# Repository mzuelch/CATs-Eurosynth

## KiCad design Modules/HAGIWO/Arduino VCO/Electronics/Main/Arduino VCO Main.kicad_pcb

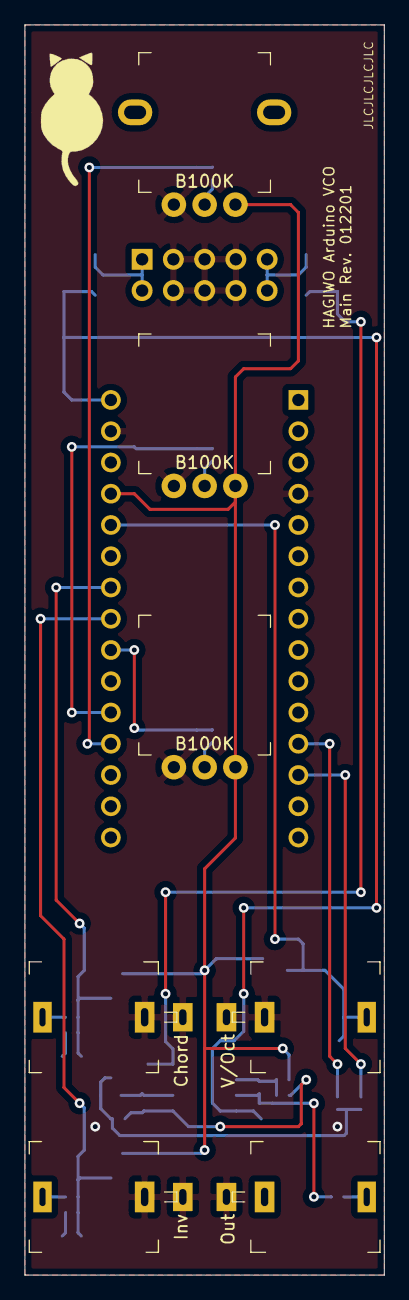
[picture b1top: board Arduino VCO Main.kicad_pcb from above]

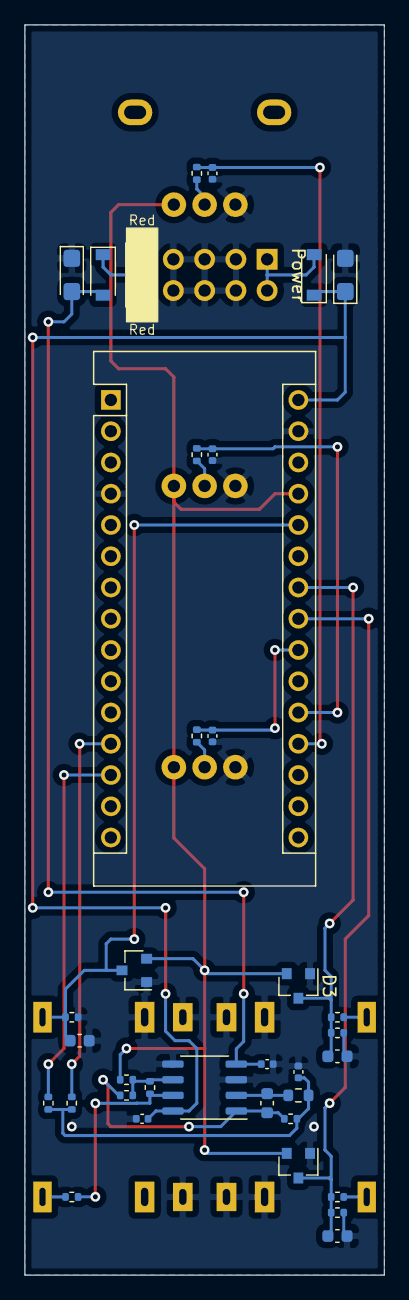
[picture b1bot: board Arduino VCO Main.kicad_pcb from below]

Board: 2 copper layers, 29.2 x 101.6 mm, 43 parts (36 on the bottom side), 25 nets.

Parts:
A1: Arduino_Nano_v3.x; Arduino_Nano
C1, C11: 10µ; CP_EIA-3216-18_Kemet-A
C2, C3, C4: 10n; C_0402_1005Metric
C5, C7, C9: 68n; C_0603_1608Metric
C6: 3.3n; C_0603_1608Metric
C8: 22n; C_0402_1005Metric
C10, C12: 100n; C_0402_1005Metric
D1, D6: B5819W SL; D_SOD-123
D2, D3, D4: BAV99; SOT-23
J1: Power; Power_2x5_Vertical
J2: V/Oct; Jack_3.5mm_QingPu_WQP-PJ301M-12
J3: Inv; Jack_3.5mm_QingPu_WQP-PJ301M-12
J4: Out; Jack_3.5mm_QingPu_WQP-PJ301M-12
J5: Chord; Jack_3.5mm_QingPu_WQP-PJ301M-12
P1: B100K; Potentiometer_AlpsAlpine_RK09L1140
P2, P3: B100K; Potentiometer_AlpsAlpine_RK09L1140_oS
R1, R2, R3, R9, R12, R15: 1k; R_0402_1005Metric
R4, R8, R10, R11, R14, R16: 100k; R_0402_1005Metric
R5: 499k; R_0402_1005Metric
R6: 3k9; R_0402_1005Metric
R7: 7k5; R_0402_1005Metric
R13: 2k7; R_0603_1608Metric
U1: TL072CDT; SO-8_3.9x4.9mm_P1.27mm

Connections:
+5V: A1.27, D2.2, D3.2, D4.2, P1.CW, P2.CW, P3.CW, R16.2
+12V: A1.30, C1.1, C10.1, D1.1, U1.8
-12V: C11.2, C12.2, D6.2, U1.4
A0: A1.19, C2.1, R1.1
A1: A1.20, C3.1, R2.1
A3: A1.22, C4.1, R3.1
A4: A1.23, C7.1, D2.3, R8.1, R9.2
A5: A1.24, C9.1, D3.3, R11.1, R12.2
A7: A1.26, C5.1, D4.3, J2.T, R4.1
D9: A1.12, R6.2
D10: A1.13, R5.2
GND: A1.4, A1.29, C1.2, C2.2, C3.2, C4.2, C5.2, C7.2, C8.2, C9.2, C10.2, C11.1, C12.1, D2.1, D3.1, D4.1, J1.GND, J2.S, J2.TN, J3.S, J3.TN, J4.S, J5.S, J5.TN, P1.CCW, P2.CCW, P3.CCW, R4.2, R8.2, R11.2, U1.3, U1.5
unnamed: C6.1, R7.2, R14.2, U1.1
unnamed: C6.2, R13.1, U1.2
unnamed: C8.1, R5.1, R6.1, R7.1, R13.2
unnamed: D1.2, J1.+12V
unnamed: D6.1, J1.-12V
unnamed: J3.T, R9.1
unnamed: J4.T, R15.1
unnamed: J5.T, R12.1
unnamed: P1.W, R1.2
unnamed: P2.W, R2.2
unnamed: P3.W, R3.2
unnamed: R10.1, R15.2, U1.7
unnamed: R10.2, R14.1, R16.1, U1.6

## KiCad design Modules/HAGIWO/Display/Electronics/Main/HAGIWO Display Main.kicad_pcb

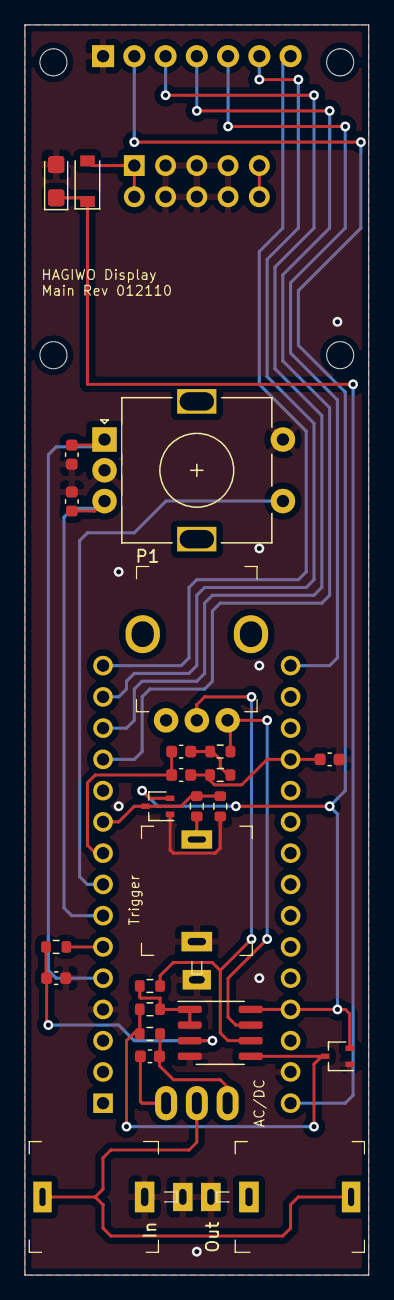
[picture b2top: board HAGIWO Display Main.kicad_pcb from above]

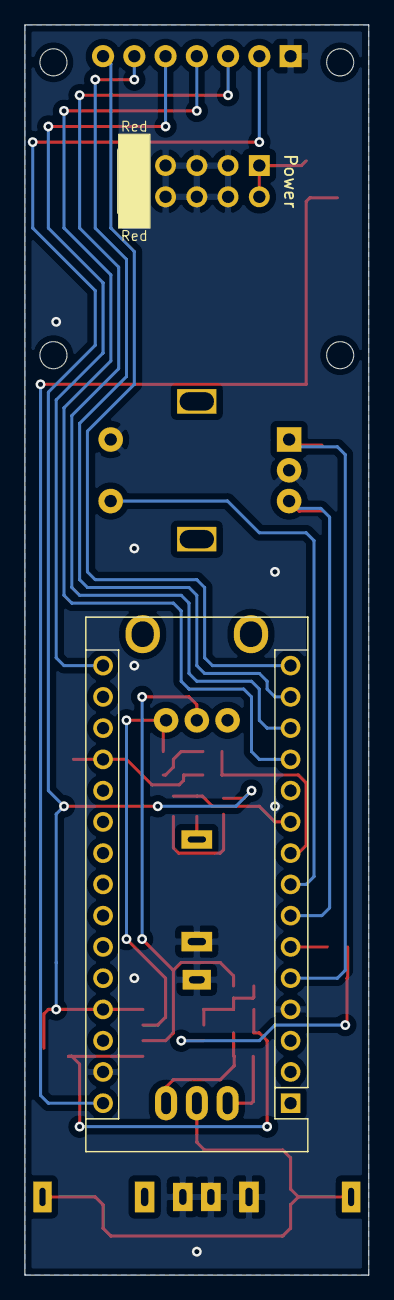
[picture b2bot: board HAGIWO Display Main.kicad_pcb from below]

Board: 2 copper layers, 27.9 x 101.6 mm, 33 parts (2 on the bottom side), 26 nets.

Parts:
A1: Arduino_Nano_v3.x; Arduino_Nano
C1: 10µF/16V; CP_EIA-3216-18_Kemet-A
C2: 1µF; C_0603_1608Metric
C3: 4.7µF; C_0603_1608Metric
C4, C5: 22n; C_0603_1608Metric
C6: 470p; C_0603_1608Metric
C7, C8: 10n; C_0603_1608Metric
D1: B5817W; D_SOD-123
D2, D3: BAV99W; SOT-323_SC-70
DISP1: MSP096x
H1, H2, H3, H4: MountingHole; MountingHole_2.2mm_M2
J1: Power; Power_2x5_Vertical
J2: Trigger; Jack_3.5mm_QingPu_WQP-PJ301M-12
J3: In; Jack_3.5mm_QingPu_WQP-PJ301M-12
J4: Out; Jack_3.5mm_QingPu_WQP-PJ301M-12
P1: B100k; Potentiometer_AlpsAlpine_RK09K1130
R1, R5: 47k; R_0603_1608Metric
R2, R7, R8: 1k; R_0603_1608Metric
R3: 100k; R_0603_1608Metric
R4, R6: 10k; R_0603_1608Metric
SW1: AC/DC; SMTS-102-2xxx
SW2: Encoder; RotaryEncoder_Alps_EC11E-Switch_Vertical_H20mm
U1: MCP6002-xSN; SOIC-8_3.9x4.9mm_P1.27mm

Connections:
+5V: A1.27, D2.2, D3.2, DISP1.VCC, U1.8
+12V: A1.30, C1.1, D1.1
+12VA: D1.2, J1.+12V
CS: A1.15, DISP1.CS
DC: A1.14, DISP1.DC
DI: A1.12, DISP1.DI
DO: A1.13, DISP1.DO
ENC_A: A1.5, C7.1, SW2.A
ENC_B: A1.7, C8.1, SW2.B
ENC_SW: A1.8, SW2.S1
Fast_PWM: A1.6, R1.2
GND: A1.4, A1.29, C1.2, C2.2, C6.2, C7.2, C8.2, D2.1, D3.1, DISP1.GND, J1.GND, J2.S, J2.TN, J3.S, J3.TN, J4.S, R3.1, SW2.C, SW2.S2, U1.4
In: A1.19, C5.1, C6.1, R8.1
LPF_Enable: A1.9, C4.2, C5.2
unnamed: C2.1, R1.1, U1.3
unnamed: C3.1, R5.2, SW1.1
unnamed: C3.2, SW1.3
unnamed: C4.1, R7.1, R8.2
unnamed: D3.3, R4.2, R5.1, U1.5
unnamed: J2.T, R2.2
unnamed: J3.T, J4.T, SW1.2
unnamed: P1.CW, R7.2, U1.7
unnamed: P1.W, R6.2, U1.6
Offset: R4.1, R6.1, U1.1, U1.2
RST: A1.16, DISP1.RESET
TriggerIn: A1.10, D2.3, R2.1, R3.2

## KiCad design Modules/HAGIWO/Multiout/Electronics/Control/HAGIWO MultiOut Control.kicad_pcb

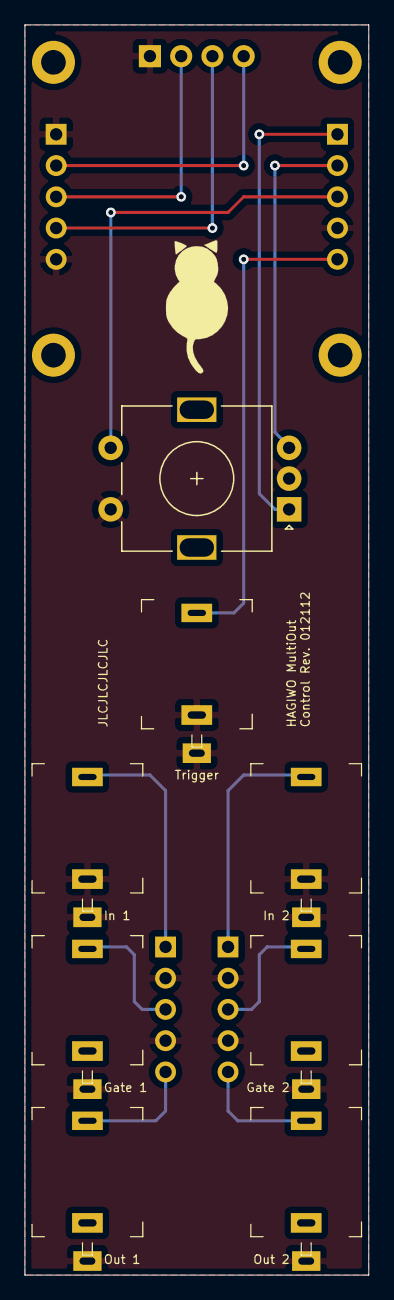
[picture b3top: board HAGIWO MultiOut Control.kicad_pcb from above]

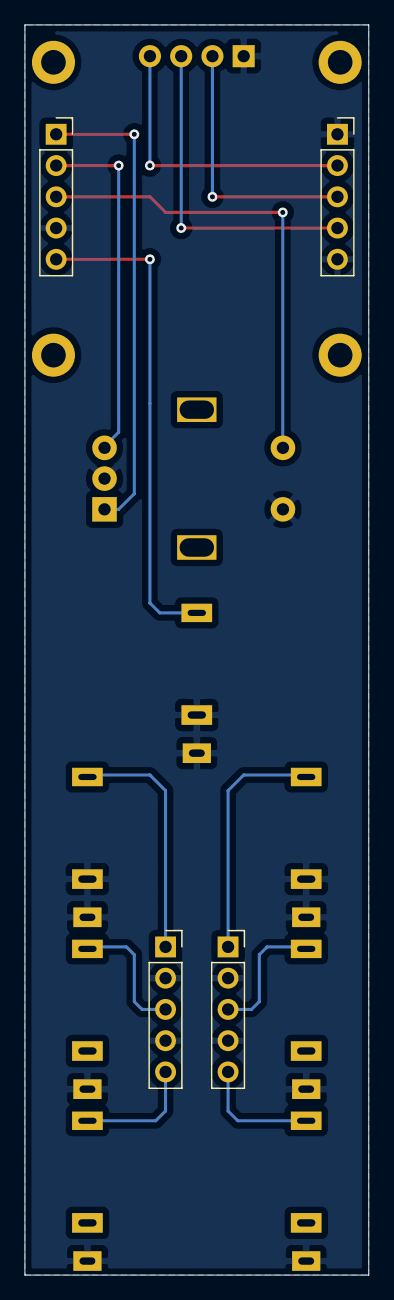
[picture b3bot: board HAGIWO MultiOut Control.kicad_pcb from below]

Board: 2 copper layers, 27.9 x 101.6 mm, 13 parts (4 on the bottom side), 14 nets.

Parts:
D1: SSD1306_4Pin; 0.96inch_OLED_MC096GX
J1: Trigger; Jack_3.5mm_QingPu_WQP-PJ301M-12
J2: In 1; Jack_3.5mm_QingPu_WQP-PJ301M-12
J3: Gate 1; Jack_3.5mm_QingPu_WQP-PJ301M-12
J4: Out 1; Jack_3.5mm_QingPu_WQP-PJ301M-12
J5: In 2; Jack_3.5mm_QingPu_WQP-PJ301M-12
J6: Gate 2; Jack_3.5mm_QingPu_WQP-PJ301M-12
J7: Out 2; Jack_3.5mm_QingPu_WQP-PJ301M-12
J8: EncTrig; PinSocket_1x05_P2.54mm_Vertical
J9: Ch. 1; PinSocket_1x05_P2.54mm_Vertical
J10: Ch. 2; PinSocket_1x05_P2.54mm_Vertical
J11: I2C; PinSocket_1x05_P2.54mm_Vertical
SW1: Enc; RotaryEncoder_Alps_EC11E-Switch_Vertical_H20mm

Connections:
+3V3: D1.VCC, J11.3
Enc_A: J8.1, SW1.A
Enc_B: J8.2, SW1.B
Enc_SW: J8.3, SW1.S1
GND: D1.GND, J1.S, J1.TN, J2.S, J2.TN, J3.S, J4.S, J5.S, J5.TN, J6.S, J7.S, J8.4, J9.2, J9.4, J10.2, J10.4, J11.1, J11.5, SW1.C, SW1.S2
Gate1: J3.T, J9.3
Gate2: J6.T, J10.3
In1: J2.T, J9.1
In2: J5.T, J10.1
Out1: J4.T, J9.5
Out2: J7.T, J10.5
SCL: D1.SCL, J11.4
SDA: D1.SDA, J11.2
Trigger: J1.T, J8.5

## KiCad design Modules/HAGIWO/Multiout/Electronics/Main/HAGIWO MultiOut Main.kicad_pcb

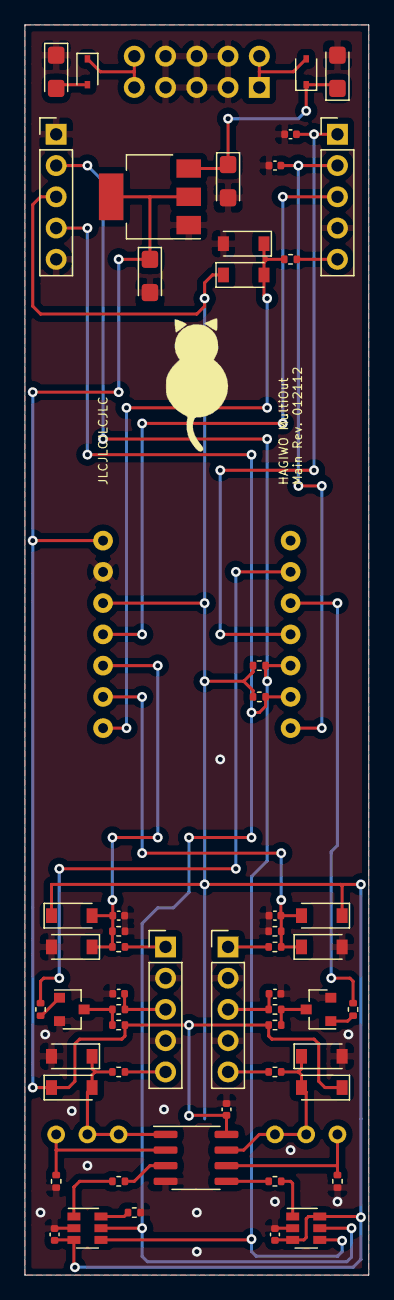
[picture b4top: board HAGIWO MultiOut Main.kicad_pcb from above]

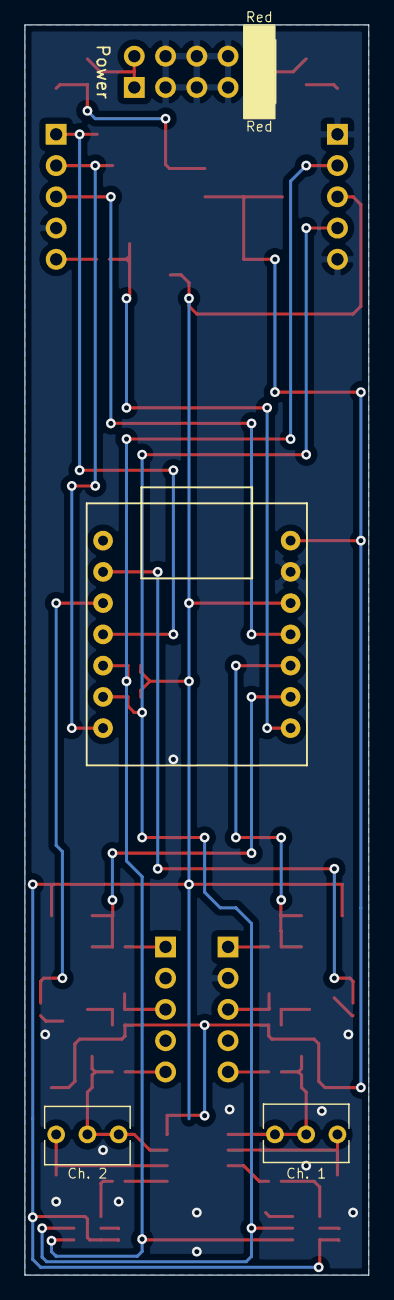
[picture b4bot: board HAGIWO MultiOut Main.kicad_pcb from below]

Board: 2 copper layers, 27.9 x 101.6 mm, 59 parts (4 on the bottom side), 37 nets.

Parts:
C1, C2, C3, C4: 10µ; CP_EIA-3216-18_Kemet-A
C5, C6, C7, C8: 10n; C_0402_1005Metric
C9, C10: 1µ; C_0402_1005Metric
C11, C12, C13: 100n; C_0402_1005Metric
D1, D2: 1N5819WS; D_SOD-323
D4, D5, D6, D7, D8, D9, D10, D11, D12, D13: BAT43W; D_SOD-123
J1: Power; Power_2x5_Vertical
J9: EncTrig; PinHeader_1x05_P2.54mm_Vertical
J10: Ch. 1; PinHeader_1x05_P2.54mm_Vertical
J11: I2C; PinHeader_1x05_P2.54mm_Vertical
J12: Ch. 2; PinHeader_1x05_P2.54mm_Vertical
Q1, Q2: MMBT3904; SOT-23
R1, R2: 3k3; R_0402_1005Metric
R3, R16, R20: 10k; R_0402_1005Metric
R4, R17: 6k8; R_0402_1005Metric
R5, R6: 220k; R_0402_1005Metric
R7, R8: 330k; R_0402_1005Metric
R9: 33k; R_0402_1005Metric
R10, R11: 1k; R_0402_1005Metric
R12, R13, R14, R15: 330R; R_0402_1005Metric
R18, R19: 470R; R_0402_1005Metric
RV1, RV2: 5k; Potentiometer_Bourns_3266Y_Vertical
U1: AMS1117-5.0; SOT-223-3_TabPin2
U2: SeeeduinoXIAOPin; Seeeduino XIAO Pin
U3, U5: MCP4725xxx-xCH; SOT-23-6
U4: MCP6002-xSN; SOIC-8_3.9x4.9mm_P1.27mm

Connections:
+3V3: C11.1, C12.1, D4.1, D6.1, D8.1, J11.3, R1.1, R2.1, U2.12, U3.3, U5.3, U5.6
+5V: C4.1, C13.1, D10.1, D12.1, R12.1, R13.1, U1.2, U2.14, U4.8
+12V: C1.1, C3.1, D1.1, U1.3
-12V: C2.2, D2.2
A7: D8.2, D9.1, R9.1, U2.8
A8: C6.1, D6.2, D7.1, R6.1, R8.2, U2.9
A9: C5.1, D4.2, D5.1, R5.1, R7.2, U2.10
D1: R10.2, U2.2
D2: R11.2, U2.3
D3: C7.1, J9.1, U2.4
D6: C8.1, J9.2, U2.7
D10: J9.3, U2.11
GND: C1.2, C2.1, C3.2, C4.2, C5.2, C6.2, C7.2, C8.2, C9.2, C10.2, C11.2, C12.2, C13.2, D5.2, D7.2, D9.2, D11.2, D13.2, J1.GND, J9.4, J10.2, J10.4, J11.1, J11.5, J12.2, J12.4, Q1.2, Q2.2, R4.1, R7.1, R8.1, R17.1, R20.1, U1.1, U2.13, U3.2, U4.4, U5.2
Gate1: C9.1, J10.3, R14.1
Gate2: C10.1, J12.3, R15.1
In1: J10.1, R5.2
In2: J12.1, R6.2
unnamed: D1.2, J1.+12V
unnamed: D2.1, J1.-12V
unnamed: D10.2, D11.1, R18.2, RV1.1, RV1.2, U4.1
unnamed: D12.2, D13.1, R19.2, RV2.1, RV2.2, U4.7
unnamed: Q1.1, R10.1
unnamed: Q1.3, R12.2, R14.2
unnamed: Q2.1, R11.1
unnamed: Q2.3, R13.2, R15.2
unnamed: R3.1, U4.3
unnamed: R3.2, U3.1
unnamed: R4.2, RV1.3, U4.2
unnamed: R16.1, U4.5
unnamed: R16.2, U5.1
unnamed: R17.2, RV2.3, U4.6
unnamed: R20.2, U3.6
Out1: J10.5, R18.1
Out2: J12.5, R19.1
SCL: J11.4, R2.2, U2.6, U3.5, U5.5
SDA: J11.2, R1.2, U2.5, U3.4, U5.4
Trigger: J9.5, R9.2

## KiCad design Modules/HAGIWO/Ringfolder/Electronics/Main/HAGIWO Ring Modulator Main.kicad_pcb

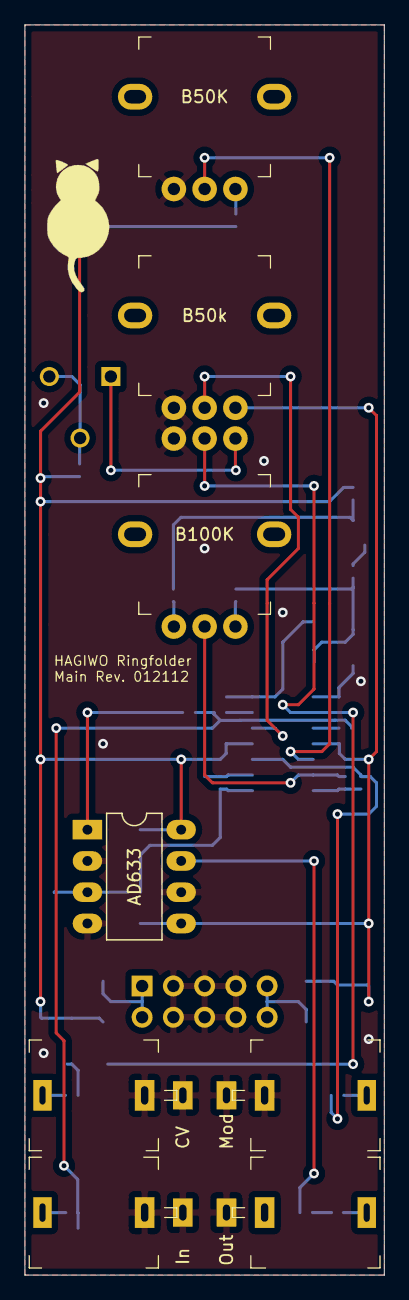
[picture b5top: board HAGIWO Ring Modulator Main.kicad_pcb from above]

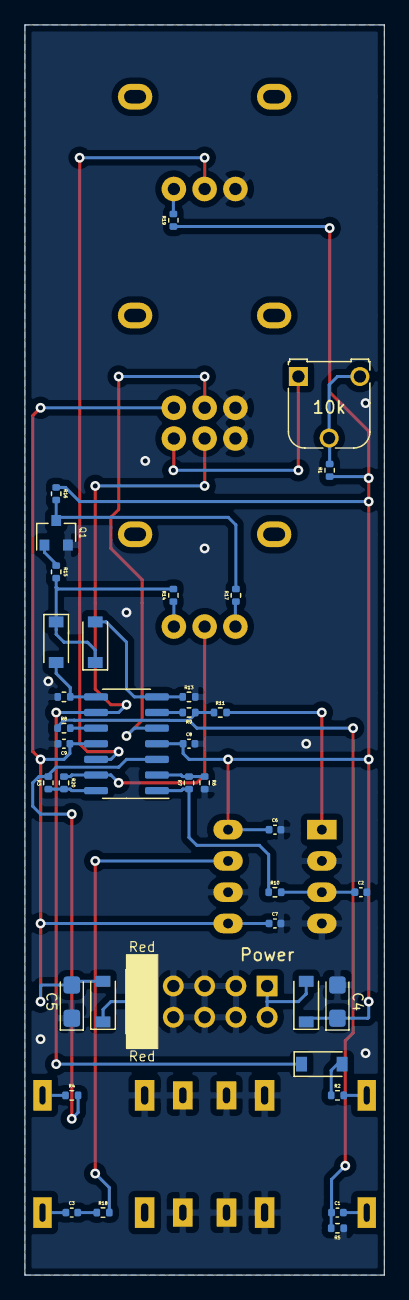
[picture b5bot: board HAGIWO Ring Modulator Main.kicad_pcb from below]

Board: 2 copper layers, 29.2 x 101.6 mm, 46 parts (38 on the bottom side), 35 nets.

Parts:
C1, C3: 1µ; C_0402_1005Metric
C2: 3n3; C_0402_1005Metric
C4, C5: 10µ/25V; CP_EIA-3216-18_Kemet-A
C6, C7, C8, C9: 100n; C_0402_1005Metric
D1, D2, D3: 1N4148; D_SOD-123
D4, D5: 1N5817; D_SOD-123
J1: CV; Jack_3.5mm_QingPu_WQP-PJ301M-12
J2: In; Jack_3.5mm_QingPu_WQP-PJ301M-12
J3: Mod; Jack_3.5mm_QingPu_WQP-PJ301M-12
J4: Out; Jack_3.5mm_QingPu_WQP-PJ301M-12
J5: Power; Power_2x5_Vertical
P1: B50k; Potentiometer_AlpsAlpine_RK09L1240
P2: B100K; Potentiometer_AlpsAlpine_RK09L1140
P3: B50K; Potentiometer_AlpsAlpine_RK09L1140
Q1: MMBT3904; SOT-23
R1, R2, R7, R10, R15: 10k; R_0402_1005Metric
R3, R4, R6, R8, R9, R11: 33k; R_0402_1005Metric
R5, R12, R13, R16, R20: 100k; R_0402_1005Metric
R14, R17, R19: 47k; R_0402_1005Metric
R18: 4k7; R_0402_1005Metric
T1: 10k; Potentiometer_Runtron_RM-065_Vertical
U1: AD633; DIP-8_W7.62mm_LongPads
U2: TL074; SOIC-14_3.9x8.7mm_P1.27mm

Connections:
+12V: C4.1, C6.2, C8.2, D4.1, R1.2, R16.2, R19.2, U1.8, U2.4
-12V: C5.2, C7.1, C9.1, D5.2, P1.CW1, U1.5, U2.11
Fold_In: R3.2, R20.1, U2.14
GND: C2.1, C4.2, C5.1, C6.1, C7.2, C8.1, C9.2, J1.S, J1.TN, J2.S, J2.TN, J3.S, J3.TN, J4.S, J5.GND, P1.CCW1, P1.CCW2, P3.CCW, Q1.2, R5.1, R6.1, R12.1, R13.1, U1.2, U1.4, U1.6
unnamed: C1.1, R5.2, R8.2, R9.2, R11.2
unnamed: C1.2, J2.T
unnamed: C2.2, R10.1, U1.3
unnamed: C3.1, J4.T
unnamed: C3.2, R18.1
unnamed: D1.1, P1.W2, U2.9
unnamed: D1.2, R2.1
unnamed: D2.1, D3.1, R14.2, R15.2
unnamed: D2.2, R12.2, U2.8
unnamed: D3.2, R13.2, U2.7
unnamed: D4.2, J5.+12V
unnamed: D5.1, J5.-12V
unnamed: J1.T, R2.2
unnamed: J3.T, R4.2
unnamed: P1.CW2, T1.1
unnamed: P1.W1, U2.5
unnamed: P2.CCW, R17.1
unnamed: P2.CW, R14.1
unnamed: P2.W, R20.2, U2.13
unnamed: P3.CW, R19.1
unnamed: P3.W, U2.12
unnamed: Q1.1, R15.1
unnamed: Q1.3, R16.1, R17.2
unnamed: R1.1, T1.2, T1.3
unnamed: R3.1, R4.1, U2.3
unnamed: R6.2, R7.2, U2.2
unnamed: R8.1, U2.10
unnamed: R9.1, U2.6
unnamed: R7.1, R10.2, U2.1
unnamed: R11.1, U1.1
unnamed: R18.2, U1.7
